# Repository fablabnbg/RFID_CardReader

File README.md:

# RFID_CardReader

A device to read member cards and activate peripheral devices.

## Documentation / Requirements
- See [doc/](doc/) subdirectory for requirements, concepts and schematics

## Software

### ESP
- Example software in subdirectory [Software_ESP](Software_ESP)
- To be built with platformio
- Use "Automaton" library for state machine and WiFi / HTTP connectivity
- Continious integration on travis-ci: 
- For details see [Software_ESP/README.md](Software_ESP/README.md)

### Webserver
 - not yet implemented
 - planning: Use simple server on Raspberry PI

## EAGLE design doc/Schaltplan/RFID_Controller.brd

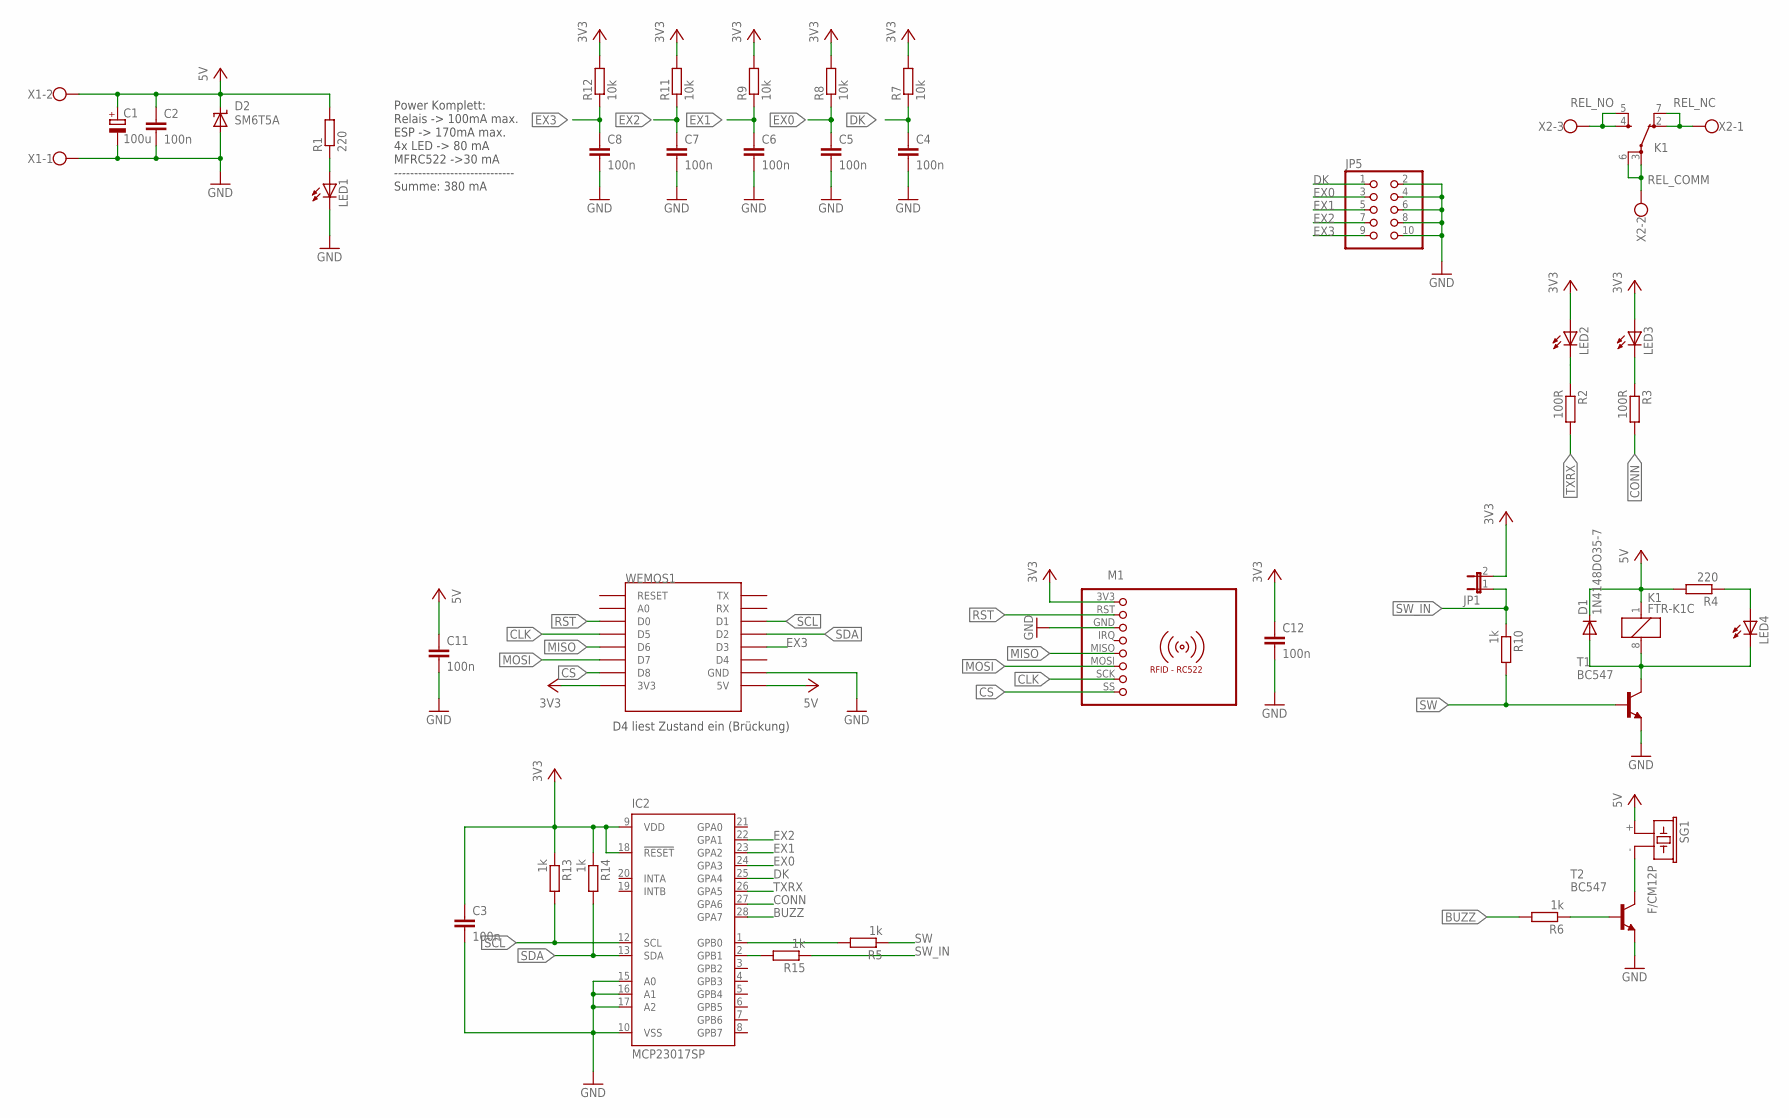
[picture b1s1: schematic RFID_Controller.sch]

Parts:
C1: 100u; E2,5-7
C2, C3, C4, C5, C6, C7, C8, C11, C12: 100n; C050-025X075
D1: 1N4148DO35-7; DO35-7
D2: SM6T5A; SMBJ
IC2: MCP23017SP; DIL28-3
JP1: JP1E; JP1
JP5: PINHD-2X5; 2X05
K1: FTR-K1C
LED1, LED2, LED3, LED4: LED3MM
M1: RFID-RC522
R1, R4: 220; 0204/7
R2, R3: 100R; 0204/7
R5, R6, R10, R13, R14, R15: 1k; 0204/7
R7, R8, R9, R11, R12: 10k; 0204/7
SG1: F/CM12P
T1, T2: BC547; TO92
WEMOS1: WEMOS-D1-MINI
X1: W237-102
X2: W237-103

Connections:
3V3: C3.1, C12.1, IC2.9 (VDD), IC2.18 (!RESET), JP1.2, LED2.A, LED3.A, M1.3V3 (1), R7.2, R8.2, R9.2, R11.2, R12.2, R13.1, R14.1, WEMOS1.3V3
5V: C1.+, C2.1, C11.1, D1.C, D2.C, K1.1, R1.2, R4.2, SG1.+ (1), WEMOS1.5V, X1.2
BUZZ: IC2.28 (GPA7), R6.2
CLK: M1.SCK (7), WEMOS1.D5
CONN: IC2.27 (GPA6), R3.2
CS: M1.SS (8), WEMOS1.D8
DK: C4.1, IC2.25 (GPA4), JP5.1, R7.1
EX0: C5.1, IC2.24 (GPA3), JP5.3, R8.1
EX1: C6.1, IC2.23 (GPA2), JP5.5, R9.1
EX2: C7.1, IC2.22 (GPA1), JP5.7, R11.1
EX3: C8.1, JP5.9, R12.1, WEMOS1.D3
GND: C1.-, C2.2, C3.2, C4.2, C5.2, C6.2, C7.2, C8.2, C11.2, C12.2, D2.A, IC2.10 (VSS), IC2.15 (A0), IC2.16 (A1), IC2.17 (A2), JP5.2, JP5.4, JP5.6, JP5.8, JP5.10, LED1.K (C), M1.GND (3), T1.1 (E), T2.1 (E), WEMOS1.GND, X1.1
MISO: M1.MISO (5), WEMOS1.D6
MOSI: M1.MOSI (6), WEMOS1.D7
unnamed: LED1.A, R1.1
unnamed: LED2.K (C), R2.1
unnamed: LED3.K (C), R3.1
unnamed: LED4.A, R4.1
unnamed: D1.A, K1.8 (2), LED4.K (C), T1.3 (C)
unnamed: R6.1, T2.2 (B)
unnamed: SG1.- (2), T2.3 (C)
unnamed: IC2.1 (GPB0), R5.2
unnamed: IC2.2 (GPB1), R15.2
REL_COMM: K1.3 (PA), K1.6 (PB), X2.2
REL_NC: K1.2 (OA), K1.7 (OB), X2.1
REL_NO: K1.4 (SA), K1.5 (SB), X2.3
RST: M1.RST (2), WEMOS1.D0
SCL: IC2.12 (SCL), R13.2, WEMOS1.D1
SDA: IC2.13 (SDA), R14.2, WEMOS1.D2
SW: R5.1, R10.2, T1.2 (B)
SW_IN: JP1.1, R10.1, R15.1
TXRX: IC2.26 (GPA5), R2.2

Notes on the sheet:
Power Komplett: Relais -> 100mA max. ESP -> 170mA max. 4x LED -> 80 mA MFRC522 ->30 mA ------------------------------ Summe: 380 mA
D4 liest Zustand ein (Brückung)

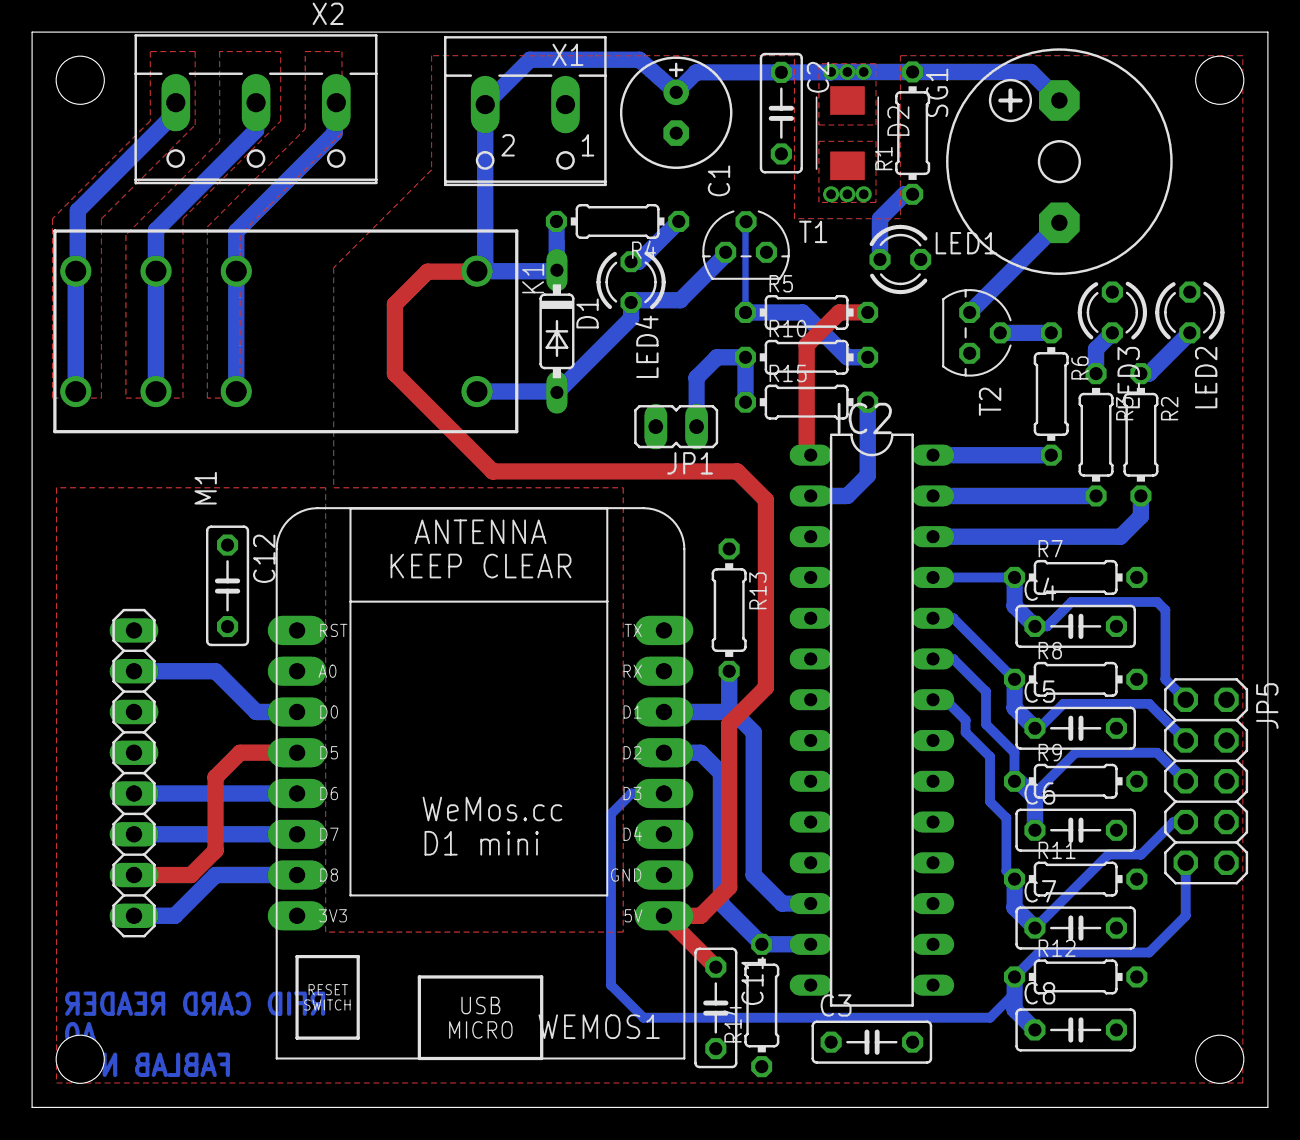
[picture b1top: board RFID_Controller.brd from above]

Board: 2 copper layers, 77.0 x 67.0 mm, 42 parts (0 on the bottom side), 32 nets.

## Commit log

2017-11-03 -first commit. Added TechSpec, board schematic and layout, pdf manuals for infos about several parts
2017-11-22 -add: I2C Expander for more GPIOs -add: input for sabotage detection ( switch for enclosure cover ) -add: 2 more inputs for possible extensions -mod: additional resistor in pull-up path of relais tra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
2017-11-22 -del: old pictures of layout and schematic -add: new pdfs for current layout and schematic
2017-11-24 -mod: 2 additional Extra GPIO's -mod: replaced 3 single 1x2 pin headers with 2x5 pin header -mod: maximized copper area of relay contacts -info: Schematic verified by Ian Hubbertz
2017-11-24 -mod: modifies according to Roberts recommendations
2017-11-26 -mod: more distance between drill and HV (upper left corner) -mod: TVS diode instead of Z-Diode -fix: additional resistor to SW Output pin to avoid short circuits. SW input pin measures now full volt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
2017-12-04 -mod: Board layout and Schematic in ELAB optimized
2017-12-04 -add: pseudo code file for first software draft (ESP)
2017-12-10 First version of ESP-Software using Automaton
    - I also restructed the documentation to doc folder and sub-folders
    - To compile, install platfomio and run "pio run", to upload run "pio
    run -t upload".
2017-12-10 First try for travis-ci
2017-12-31 Netzteil dummy.
2017-12-31 MFRC522-Module dummy. Hope 60mm x 40mm is correct.
2017-12-31 Relais dummy
2018-01-04 first study how things could fit inside...
2018-01-04 second study how things could fit inside... have the sensitiv area more in the center of the box
2018-01-04 second study how things could fit inside... have the sensitiv area really in the center of the box
2018-01-04 small adjustments.
2018-01-04 two halfs of the housing done!
2018-01-07 screws, interieor, clearances
2018-01-07 screenshot added.
2018-01-08 moved front screw from left to right, so that both rails are in left housing. Added access openings in the rails for the screws below. All components are built into the left housing part. The right w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
2018-01-08 Create README.MD for software: Explain how to build and give overview about SW architecture.
2018-01-08 Set D1_Mini as default build
2018-01-09 Truecon version of the left part added
2018-01-09 README.md: fixed typo, add link to Software_ESP
2018-01-09 screenshots added.
2018-01-09 Imported 3D+File+NAC3PX.stp 3D+File+SCNAC-PX.stp Strichzeichnung+NAC3MX-W.png from Neutrik. Used with permission:
    neutrik@neutrik.de <neutrik@neutrik.de>
    12:05 (vor 3 Stunden)
    an mich
    Guten Tag Herr Weigert,
    vielen Dank für Ihre Nachricht und Ihr Vorhaben. Die Einbindung der STEP-Dateien geht so in Ordnung.
    Mit freundlichen Grüßen | Best regards
2018-01-10 Progress for #5: Initial Commit
2018-01-11 5mm tieferes gehäuse. Sollbruchstellen drin.
2018-01-20 Small improvements
2018-01-20 -mod: update to v1.0 final version of schematic and layout
2018-01-21 Changes for testing
2018-01-21 No more BIP BIP at connect
2018-08-13 svg der linken seite dazu, Leider immernoch Pultform.
2018-08-19 -add: docs, python server scripts, additional source code for RFID card reader -mod: RFID card reader source code implemented
2018-08-19 -mod: fixed a bug in the schematic/layout
